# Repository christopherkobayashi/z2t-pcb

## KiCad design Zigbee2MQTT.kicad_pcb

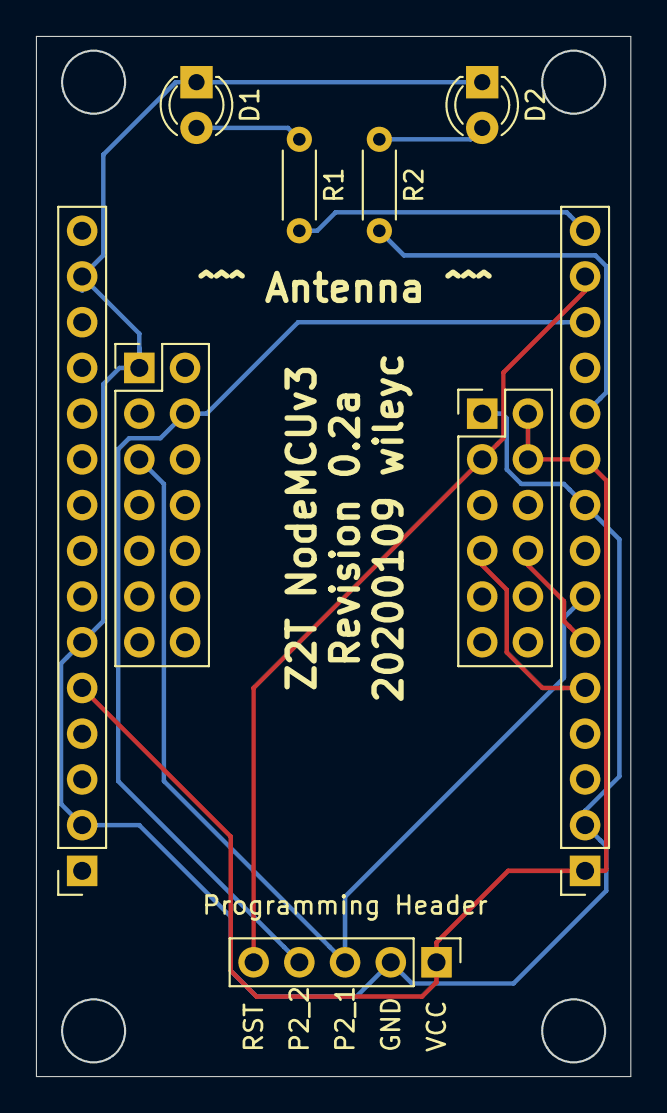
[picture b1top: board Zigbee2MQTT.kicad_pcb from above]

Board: 2 copper layers, 33.0 x 57.8 mm, 9 parts (0 on the bottom side), 11 nets.

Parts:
D1, D2: LED; LED_D3.0mm
J1, J2: NodeMCU; PinSocket_1x15_P2.54mm_Vertical
J3: CC2530; PinHeader_2x07_P2.54mm_Vertical
J4: CC2530; PinHeader_2x06_P2.54mm_Vertical
J5: Programming Header; PinHeader_1x05_P2.54mm_Vertical
R1: 330; R_Axial_DIN0204_L3.6mm_D1.6mm_P5.08mm_Horizontal
R2: R; R_Axial_DIN0204_L3.6mm_D1.6mm_P5.08mm_Horizontal

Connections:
unnamed: D1.1, D2.1, J1.2, J1.9, J2.2, J2.6, J2.14, J3.1, J4.1, J5.2
unnamed: D1.2, R1.1
unnamed: D2.2, R2.1
unnamed: J1.1, J1.10, J2.5, J4.2, J4.4, J5.1
unnamed: J1.5, J4.7
unnamed: J1.6, J4.8
unnamed: J1.7, J3.5, J5.3
unnamed: J1.11, R2.2
unnamed: J1.13, J3.4, J5.4
unnamed: J1.14, J4.3, J5.5
unnamed: J1.15, R1.2

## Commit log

2020-01-09 Initial commit.
2020-01-10 Update gerbers.
